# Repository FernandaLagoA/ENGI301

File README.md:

# ENGI301

Repository for ENGI301 course work”

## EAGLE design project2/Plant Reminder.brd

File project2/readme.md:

**Plant Reminder Box**

ENGI 301 Course Project 2

Fernanda Lago Arroyo

This github repository file summarizes the components of this folder, which act as supporting files for the PCB design of my plant reminder board project.

This folder contains the library, schematic, and board for the project, as a Bill of Materials.

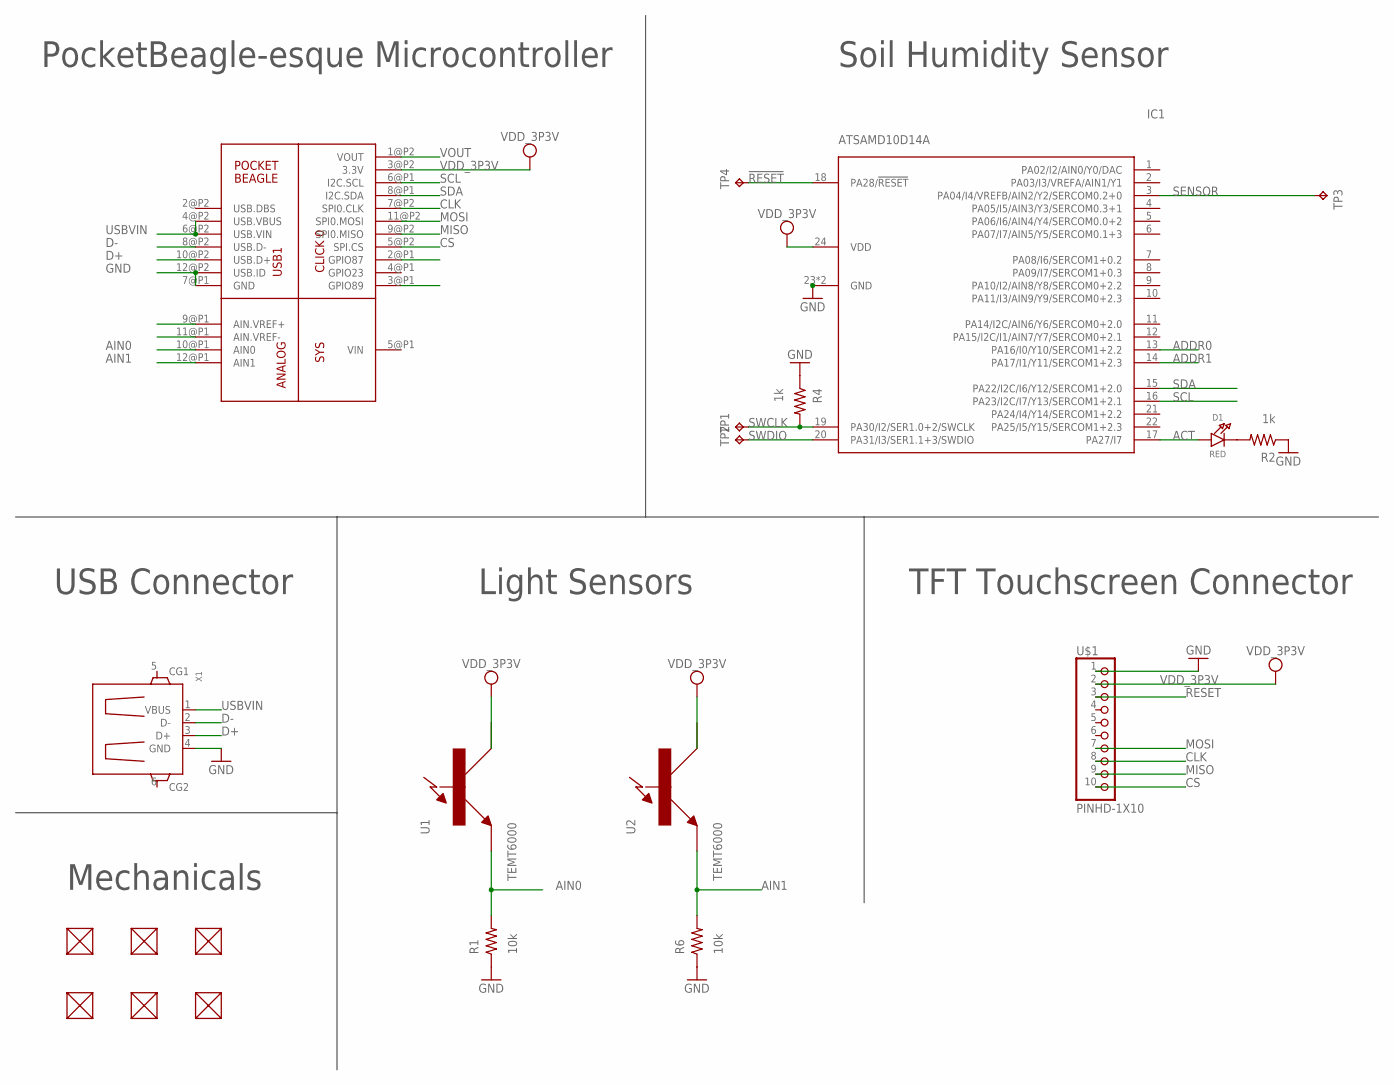
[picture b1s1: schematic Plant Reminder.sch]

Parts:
D1: RED; CHIPLED_0805_NOOUTLINE
FUD1, FUD2, FUD3, FUD4, FUD5, FUD6: FIDUCIAL; FIDUCIAL_40MIL
IC1: ATSAMD10D14A; QFN24_4MM
R1, R6: 10k; R0402
R2, R4: 1k; R0402
TP1, TP2, TP4: TPTP15R; TP15R
TP3: TPTP10R; TP10R
U1, U2: TEMT6000
U3: POCKETBEAGLE
U$1: PINHD-1X10; 1X10-BIG
X1: GHI2_USB_HOST_W/CHASSIS_GND; GHI2_USB_HOST_HORIZONTAL_W/CHASSIS_GND

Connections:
!RESET: IC1.18 (PA28/!RESET), TP4.TP
ACT: D1.A, IC1.17 (PA27/I7)
ADDR0: IC1.13 (PA16/I0/Y10/SERCOM1+2.2)
ADDR1: IC1.14 (PA17/I1/Y11/SERCOM1+2.3)
AIN0: R1.2, U1.P$2, U3.10@P1 (AIN0)
AIN1: R6.2, U2.P$2, U3.12@P1 (AIN1)
CLK: U3.7@P2 (SPI0.CLK), U$1.8
CS: U3.5@P2 (SPI.CS), U$1.10
D+: U3.10@P2 (USB.D+), X1.3 (D+)
D-: U3.8@P2 (USB.D-), X1.2 (D-)
GND: IC1.23 (GND), IC1.THERM (GND), R1.1, R2.1, R4.1, R6.1, U3.7@P1 (GND), U3.12@P2 (USB.ID), U$1.1, X1.4 (GND)
MISO: U3.9@P2 (SPI0.MISO), U$1.9
MOSI: U3.11@P2 (SPI0.MOSI), U$1.7
unnamed: D1.C, R2.2
RESET: U3.2@P1 (GPIO87), U$1.3
SCL: IC1.16 (PA23/I2C/I7/Y13/SERCOM1+2.1), U3.6@P1 (I2C.SCL)
SDA: IC1.15 (PA22/I2C/I6/Y12/SERCOM1+2.0), U3.8@P1 (I2C.SDA)
SENSOR: IC1.3 (PA04/I4/VREFB/AIN2/Y2/SERCOM0.2+0), TP3.TP
SWCLK: IC1.19 (PA30/I2/SER1.0+2/SWCLK), R4.2, TP1.TP
SWDIO: IC1.20 (PA31/I3/SER1.1+3/SWDIO), TP2.TP
USBVIN: U3.4@P2 (USB.VBUS), U3.6@P2 (USB.VIN), X1.1 (VBUS)
VDD_3P3V: IC1.24 (VDD), U1.P$1, U2.P$1, U3.3@P2 (3.3V), U$1.2
VOUT: U3.1@P2 (VOUT)

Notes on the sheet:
USB Connector
Light Sensors
TFT Touchscreen Connector
Soil Humidity Sensor
PocketBeagle-esque Microcontroller
Mechanicals

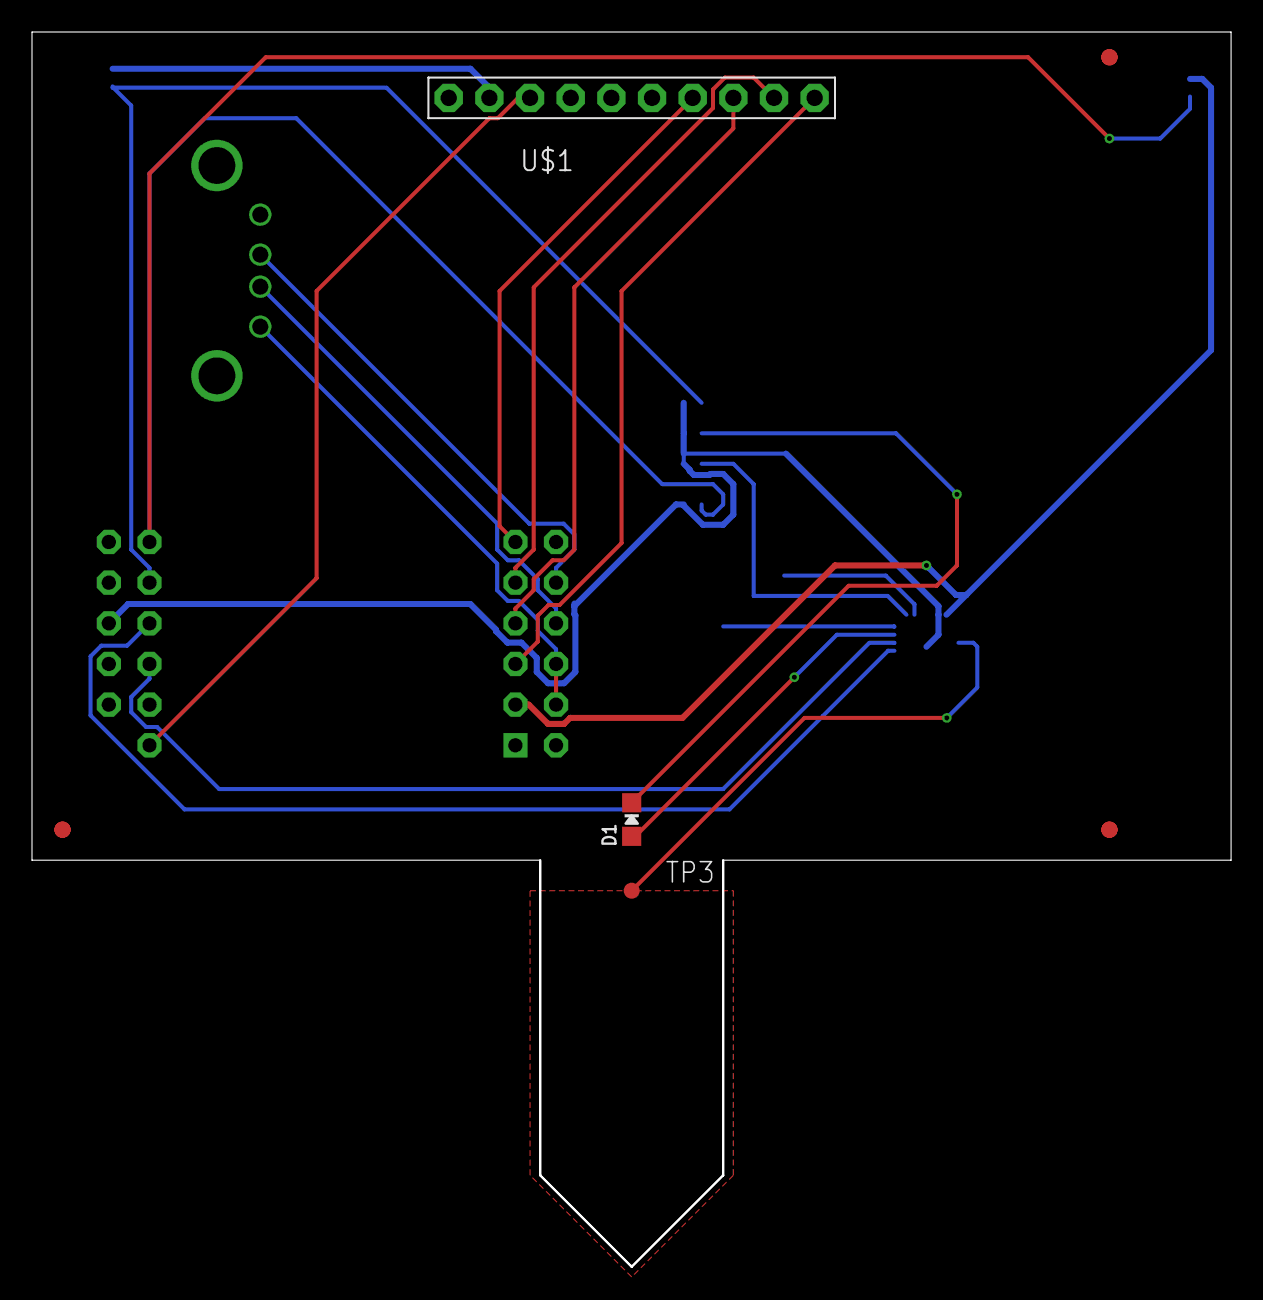
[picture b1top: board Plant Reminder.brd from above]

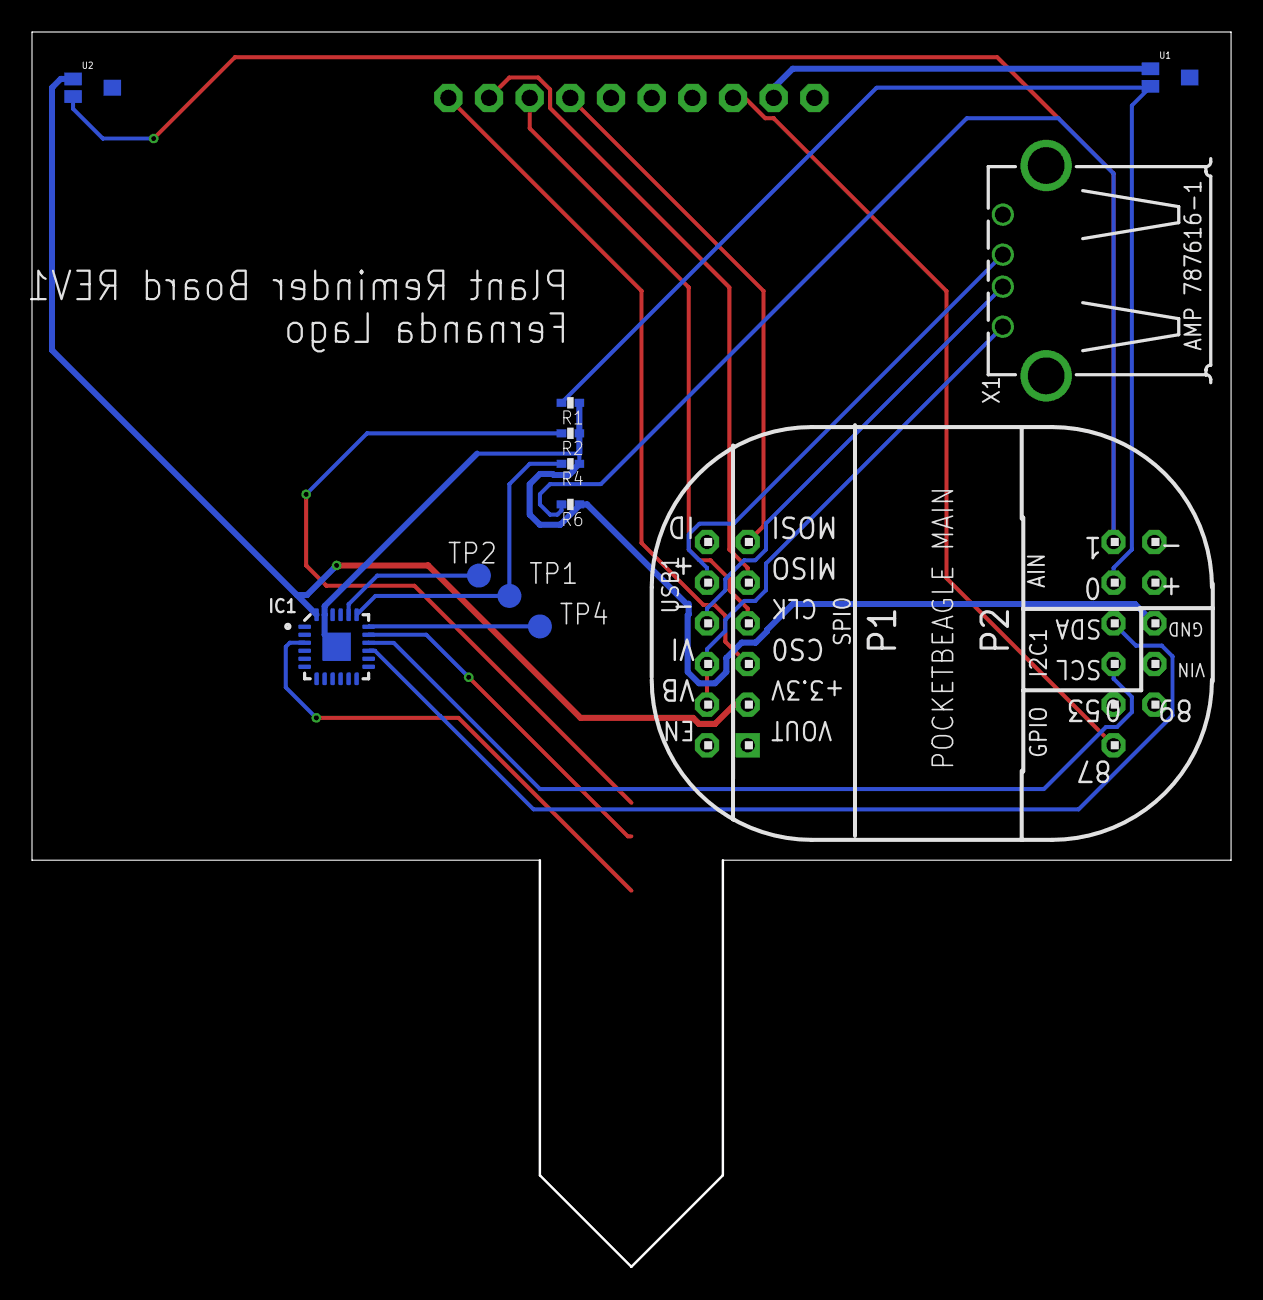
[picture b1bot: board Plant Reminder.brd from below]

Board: 4 copper layers, 74.8 x 77.1 mm, 21 parts (12 on the bottom side), 20 nets.

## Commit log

2020-09-28 Initial commit for Simple Calculator
2020-09-28 Initial Commit for Blink LED
2020-11-04 test for me
2020-11-04 Updated Project Proposal
2020-11-06 Push sh file
2020-11-06 push main.py
2020-11-06 Shell script for autobooting device
2020-11-06 Final code
2020-12-01 Updated proposal
2020-12-15 Schematic PDF
2020-12-15 Create ji
    jo
2020-12-15 Gerbers
2020-12-15 Create hi
2020-12-15 Rename project2/Plant Reminder.brd to project2/EAGLE/Plant Reminder.brd
2020-12-15 Rename project2/Plant Reminder.lbr to project2/EAGLE/Plant Reminder.lbr
2020-12-15 Rename project2/Plant Reminder.sch to project2/EAGLE/Plant Reminder.sch
2020-12-15 Create MFG

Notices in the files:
parts and their libraries:
microbuilder: This work is placed in the public domain, and may be freely used for commercial and non-commercial work with the following conditions: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
